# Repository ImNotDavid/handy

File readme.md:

# HANDY

## Overview
The Haptically-enabled and Afforable framework to control of Non-anthropomorphic robot manipulators for Data gatheringY (HANDY) is a very affordable data glove and ROS software stack to allow anyone to capture dexterous manipulation data.  

## Hardware 

The 3d model can be found at [this](https://cad.onshape.com/documents/4283529db481f6427532362c/w/a5ad88a1f793d7bc8f76de6a/e/f981b522771d813f689838bc) public onshape project. 

The lenghts of the linkages can be changed by editing variables in the `Passive Link` file or configuration values in `Main Assembly`. The size of the finger mounts can be edited similarly in `Finger Trap Net`. It is highly recommended to use [onshape-to-robot](https://github.com/Rhoban/onshape-to-robot) to convert the assembly into a URDF. The assembly, `URDF` has already been set up for this purpose and the config file [here](handy_ros2\urdf\config.json) has been configured to point to the correct file. You will need to change this to your own URL if you are making modifications. 
All parts can be printed in PLA at 0.16mm layer height. The following off the shelf components are required to assemble the Handy (5 fingered configuration):
- 10 of 6mm x 1mm diametrically magnetised magnet (found [here](https://www.first4magnets.com/product/6mm-dia-x-1mm-thick-diametrically-magnetised-n42-neodymium-magnet-20413)) 
- 20 of M2x3.2x2.5mm heat set insert with OD 
- 20 M2x6mm screws 
- 1 Mini Breadboard
- ESP32-S3 pyqt 

### PCB
All the gerber files for the PCB are found [here](pcb\output\handy_gbr.zip) and can be ordered from a manufacturer like JLCPCB for a low price. The component list is included in the KiCad project. 

# Software

## Firmware

The firmware exists as a platformio project in the [`firmware`](firmware) folder. This can be modified to work on any ESP-32 based microcontroller by selecting the appropriate chip in `platformio.ini`. 

## ROS

The ROS nodes are written for ROS2 Humble. To install, simply clone this repo into your `ros_ws/src/` folder and `colcon build` in your workspace. Note that rosdeps are not properly setup so some work may need to done manually installing required python packages. 

After sourcing the workspace, running `ros2 launch handy handy.launch.py` should deploy the software stack including the kinematic mapping to 2 fingered manipulator. This can be visualised in rviz. 

# Videos
Here are some examples of Handy being used for manipulation tasks:

https://github.com/user-attachments/assets/99e4fd3a-1bce-4f82-9469-66eb39cce375

https://github.com/user-attachments/assets/1d073916-30b5-41df-a31d-748b461f2f68

# Contact
If you have any problems (I suspect you will), feel free to reach out to me through [email](mailto:dc1021@ic.ac.uk) or [discord](https://discord.gg/3YKPjgskS3).

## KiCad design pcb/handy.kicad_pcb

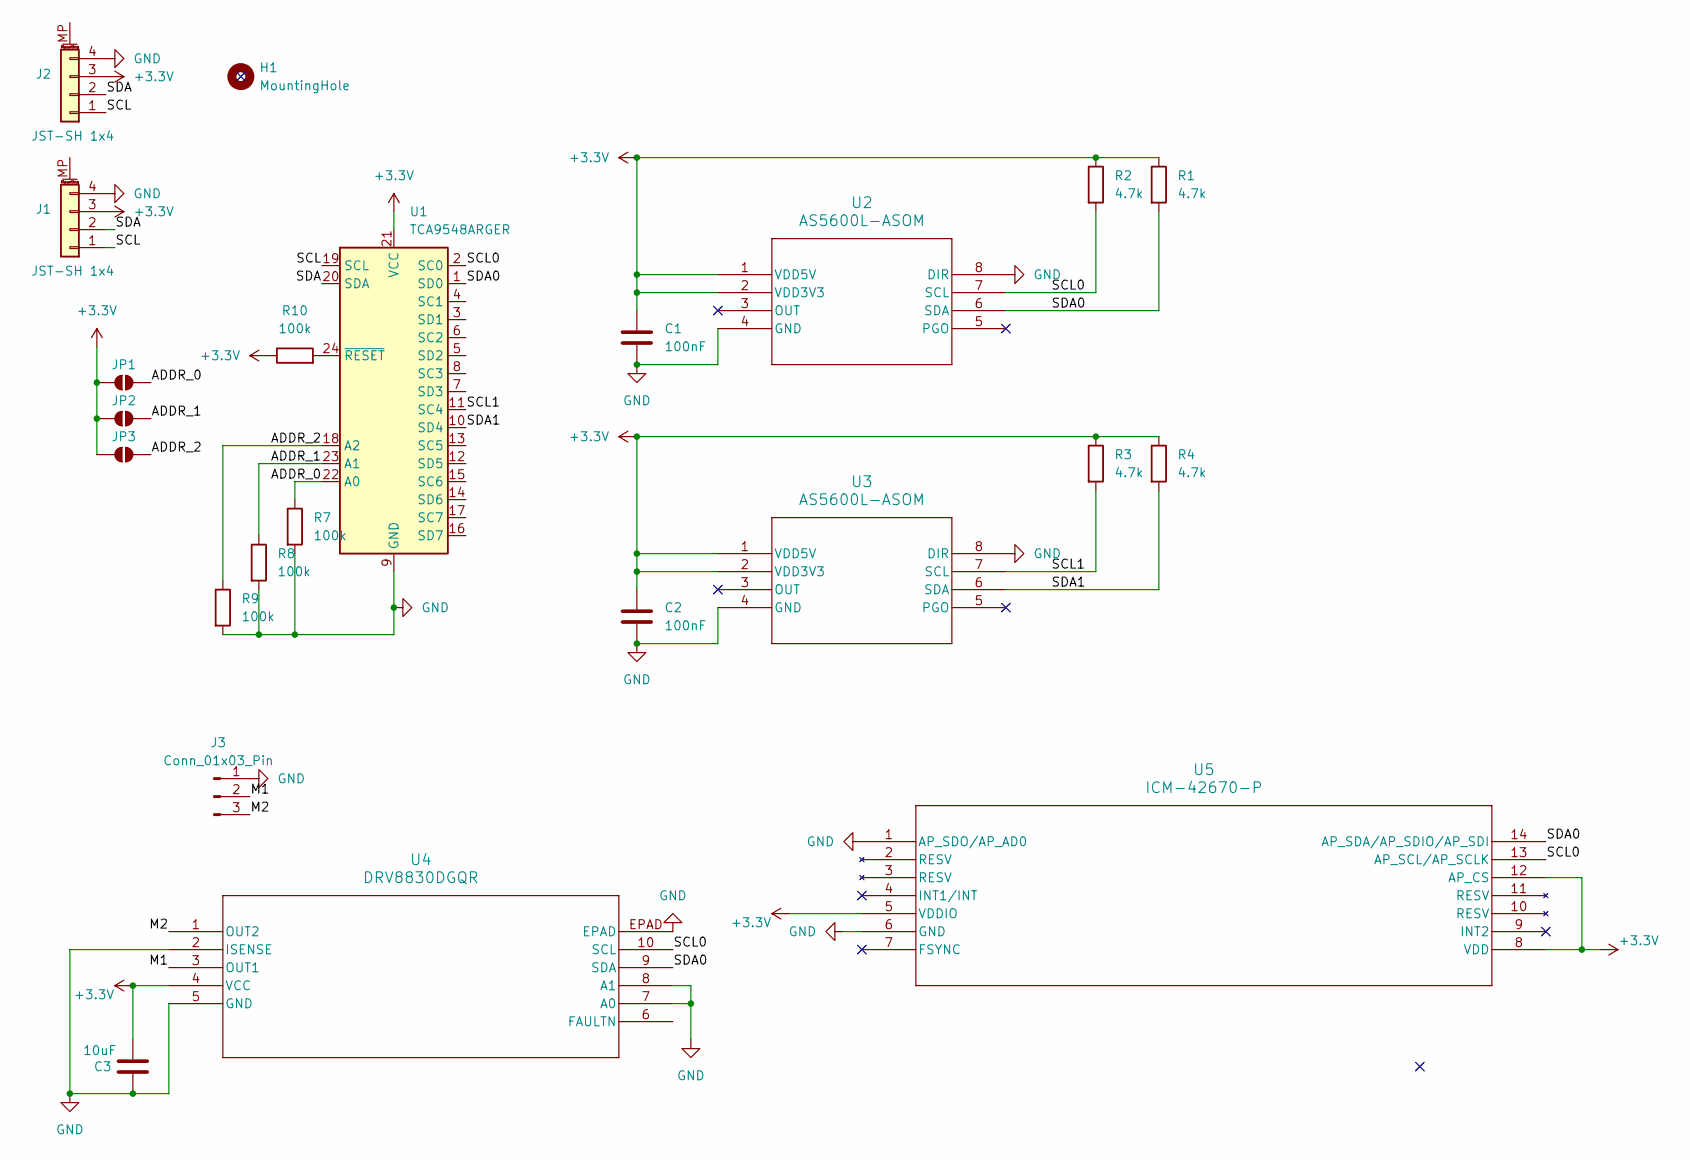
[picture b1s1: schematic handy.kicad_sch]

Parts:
C1, C2: 100nF; C_0603_1608Metric
C3: 10uF; C_0603_1608Metric
H1: MountingHole; MountingHole_2.2mm_M2_ISO14580_Pad
J1, J2: JST-SH 1x4; JST_SH_BM04B-SRSS-TB_1x04-1MP_P1.00mm_Vertical
J3: Conn_01x03_Pin; PinSocket_1x03_P2.00mm_Vertical
JP1, JP2, JP3: SolderJumper-2_P1.3mm_Open_TrianglePad1.0x1.5mm
R1, R2, R3, R4: 4.7k; R_0603_1608Metric
R7, R8, R9, R10: 100k; R_0603_1608Metric
U1: TCA9548ARGER; Texas_RGE0024C_VQFN-24-1EP_4x4mm_P0.5mm_EP2.1x2.1mm
U2, U3: AS5600L-ASOM; AS5600L-ASOM_AMS
U4: DRV8830DGQR; DGQ10_2P18X1P72
U5: ICM-42670-P; LGA14_2.5X3X0.76_IVS

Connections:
+3.3V: C1.1, C2.1, C3.2, J1.3, J2.3, JP1.2 (B), JP2.1 (A), JP3.1 (A), R1.1, R2.1, R3.1, R4.1, R10.1, U1.21 (VCC), U2.1 (VDD5V), U2.2 (VDD3V3), U3.1 (VDD5V), U3.2 (VDD3V3), U4.4 (VCC), U5.5 (VDDIO), U5.8 (VDD), U5.12 (AP_CS)
/ADDR_0: JP1.1 (A), R7.1, U1.22 (A0)
/ADDR_1: JP2.2 (B), R8.1, U1.23 (A1)
/ADDR_2: JP3.2 (B), R9.1, U1.18 (A2)
/M1: J3.2, U4.3 (OUT1)
/M2: J3.3, U4.1 (OUT2)
/SCL: J1.1, J2.1, U1.19 (SCL)
/SCL0: R2.2, U1.2 (SC0), U2.7 (SCL), U4.10 (SCL), U5.13 (AP_SCL/AP_SCLK)
/SCL1: R3.2, U1.11 (SC4), U3.7 (SCL)
/SDA: J1.2, J2.2, U1.20 (SDA)
/SDA0: R1.2, U1.1 (SD0), U2.6 (SDA), U4.9 (SDA), U5.14 (AP_SDA/AP_SDIO/AP_SDI)
/SDA1: R4.2, U1.10 (SD4), U3.6 (SDA)
GND: C1.2, C2.2, C3.1, J1.4, J2.4, J3.1, R7.2, R8.2, R9.2, U1.9 (GND), U2.4 (GND), U2.8 (DIR), U3.4 (GND), U3.8 (DIR), U4.2 (ISENSE), U4.5 (GND), U4.7 (A0), U4.8 (A1), U4.EPAD, U5.1 (AP_SDO/AP_AD0), U5.6 (GND)
unnamed: R10.2, U1.24 (~RESET)

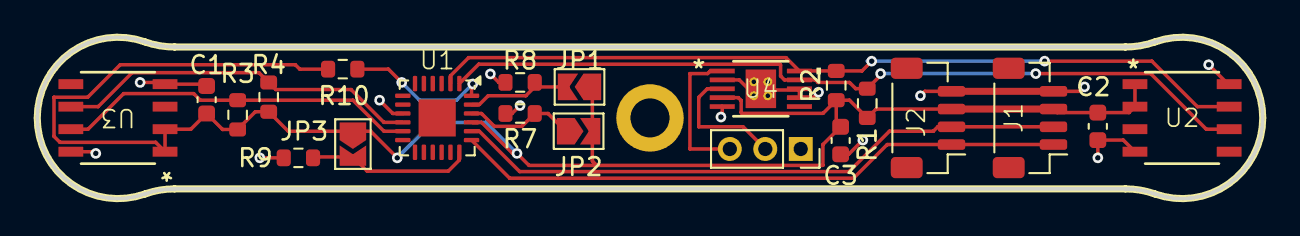
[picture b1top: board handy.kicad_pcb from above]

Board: 2 copper layers, 69.1 x 9.1 mm, 22 parts (0 on the bottom side), 14 nets.

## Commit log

2025-05-04 added as5600 footprint
2025-05-04 encoders and outline
2025-05-05 first draft
2025-05-05 fuck my chungus life
2025-05-05 routed without imu
2025-05-05 added missing pullup and capacitor
2025-05-05 added graphics
2025-05-06 Add gbr files and fixed silkscreen
2025-05-06 Changed via spacing
2025-05-13 fixed resistor values
2025-05-15 reformat project
2025-05-19 multiple fingers with offset
2025-05-19 urdf
2025-05-19 ros2 node empty folder
2025-05-19 ros2 basic package
2025-05-19 joint bridge base code
2025-05-20 handy bridge complete
2025-05-21 imu integration
2025-06-01 DPALI Implementation
2025-06-01 increased polling rate, added imu
2025-06-01 removed custom USB ID
2025-06-01 decreased latency
2025-06-02 haptic test
2025-06-02 adjusted for 3 fingers
2025-06-03 updated pinky offsets
2025-06-04 data benchmarking
2025-06-15 figure graphing
2025-06-15 added pinky
2025-06-15 websocket bridge
2025-06-15 websocket bridge ros
2025-06-15 Open Source
2025-06-15 Update readme.md
    Fixed videos
2025-06-15 Update readme.md
    More contrived acronym
2025-06-15 Update readme.md
    even more contrived
2025-06-16 wireless through esp-now
2025-06-16 fixed typo
2025-06-17 driver
2025-06-22 websocket bridge in launch
